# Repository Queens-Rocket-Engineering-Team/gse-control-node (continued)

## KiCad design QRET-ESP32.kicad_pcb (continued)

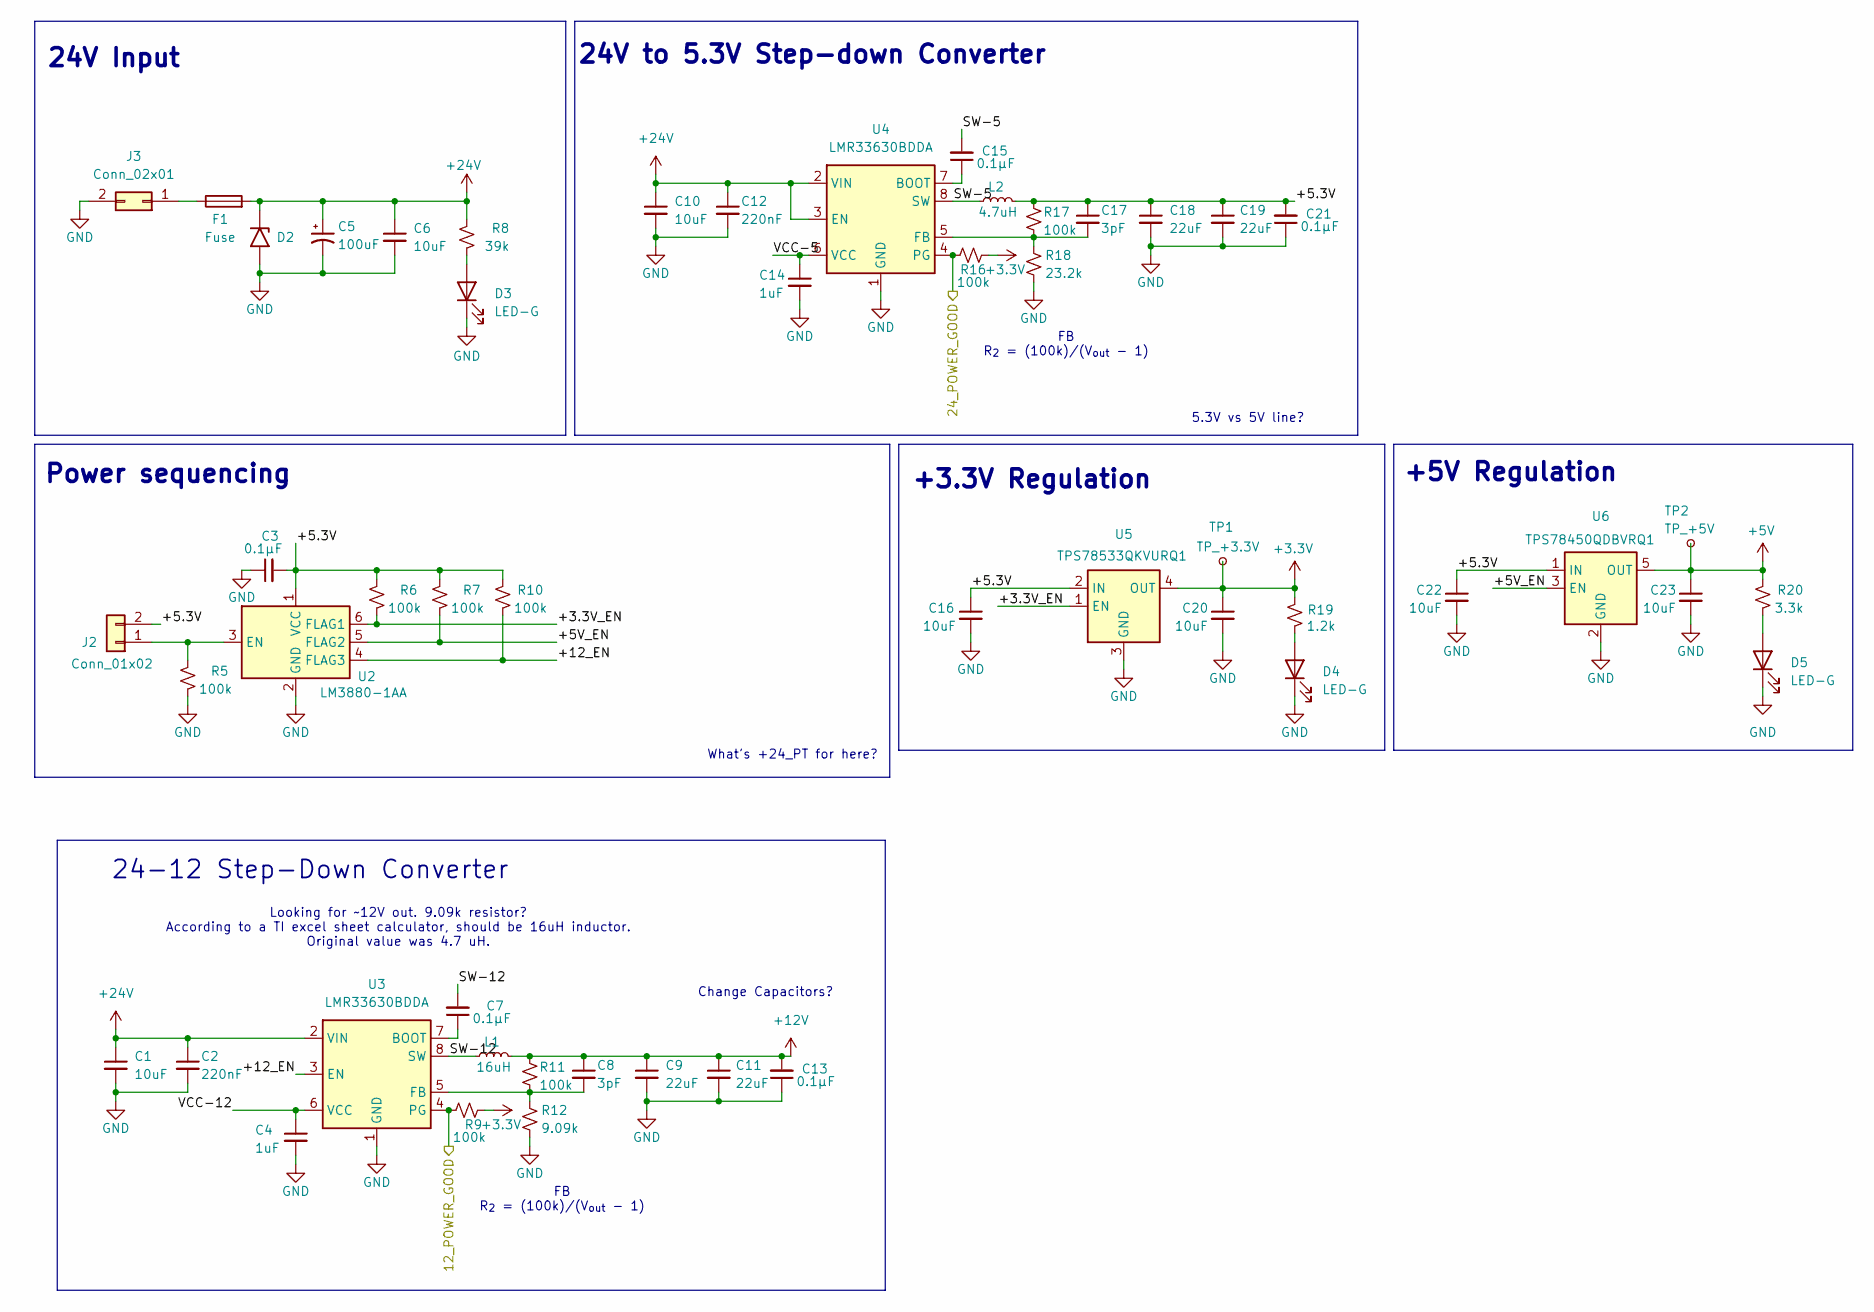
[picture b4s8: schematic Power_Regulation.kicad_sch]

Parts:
C1, C10: 10uF; C_1206_3216Metric; Voltage 50V; LCSC C13585
C2, C12: 220nF; C_0805_2012Metric; Voltage 50V; LCSC C5378
C3, C7, C13, C15, C21: 0.1μF; C_0402_1005Metric; MPN CL05B104KO5NNNC; LCSC C307331
C4, C14: 1uF; C_0603_1608Metric; LCSC C29936
C5: 100uF; CP_Elec_10x10; LCSC C161937
C6: 10uF; C_1812_4532Metric; Voltage 50V
C8, C17: 3pF; C_0603_1608Metric; LCSC C695157
C9, C11, C18, C19: 22uF; C_0805_2012Metric; LCSC C602037
C16, C20, C22, C23: 10uF; C_0805_2012Metric; LCSC C15850
D2: SMCJ26A-13-F; D_SMC; LCSC C135156
D3, D4, D5: LED-G; LED_0805_2012Metric; LCSC C2297
F1: Fuse; Fuseholder_Blade_Mini_Keystone_3568
J2: Conn_01x02; Molex_Micro-Fit_3.0_43650-0215_1x02_P3.00mm_Vertical
J3: Conn_02x01; Molex_Mini-Fit_Jr_5566-02A_2x01_P4.20mm_Vertical
L1: 16uH; L_Bourns_SRP7028A_7.3x6.6mm; LCSC C840529
L2: 4.7uH; L_Bourns_SRP7028A_7.3x6.6mm; LCSC C840529
R5, R6, R7, R10: 100k; R_0603_1608Metric
R8: 39k; R_0402_1005Metric
R9, R11, R16, R17: 100k; R_0603_1608Metric; MPN 0402WGJ0103TCE; LCSC C25531
R12: 9.09k; R_0603_1608Metric; MPN 0402WGF3301TCE; LCSC C25890
R18: 23.2k; R_0603_1608Metric; MPN 0402WGF3301TCE; LCSC C25890
R19: 1.2k; R_0402_1005Metric
R20: 3.3k; R_0402_1005Metric
TP1: TP_+3.3V; TestPoint_Pad_D1.0mm
TP2: TP_+5V; TestPoint_Pad_D1.0mm
U2: LM3880-1AA; SOT-23-6; LCSC C486059
U3, U4: LMR33630BDDA; Texas_HSOP-8-1EP_3.9x4.9mm_P1.27mm_ThermalVias; LCSC C544370
U5: TPS78533QKVURQ1; TO-252-4; LCSC C3748131
U6: TPS78450QDBVRQ1; SOT-23-5; LCSC C2877783

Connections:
12V_GOOD: R9.1, U3.4 (PG); also elsewhere on the board
24V_GOOD: R16.1, U4.4 (PG); also elsewhere on the board
+5V: C23.1, R20.2, TP2.1, U6.5 (OUT); also elsewhere on the board
+12V: C8.1, C9.1, C11.1, C13.2, L1.2, R11.1; also elsewhere on the board
+24V: C1.1, C2.1, C5.1, C6.1, C10.1, C12.1, D2.1 (A1), F1.2, R8.2, U3.2 (VIN), U4.2 (VIN), U4.3 (EN); also elsewhere on the board
/Power_Regulation/+3.3V_EN: R6.1, U2.6 (FLAG1), U5.1 (EN)
/Power_Regulation/+5.3V: C3.2, C16.1, C17.1, C18.1, C19.1, C21.2, C22.1, J2.2, L2.2, R6.2, R7.2, R10.2, R17.1, U2.1 (VCC), U5.2 (IN), U6.1 (IN)
/Power_Regulation/+5V_EN: R7.1, U2.5 (FLAG2), U6.3 (EN)
/Power_Regulation/+12_EN: R10.1, U2.4 (FLAG3), U3.3 (EN)
/Power_Regulation/SW-5: C15.2, L2.1, U4.8 (SW)
/Power_Regulation/SW-12: C7.2, L1.1, U3.8 (SW)
/Power_Regulation/VCC-5: C14.1, U4.6 (VCC)
/Power_Regulation/VCC-12: C4.1, U3.6 (VCC)
unnamed: D3.2 (A), R8.1
unnamed: D4.2 (A), R19.1
unnamed: D5.2 (A), R20.1
unnamed: J2.1, R5.2, U2.3 (EN)
unnamed: F1.1, J3.1
unnamed: C7.1, U3.7 (BOOT)
unnamed: C8.2, R11.2, R12.1, U3.5 (FB)
unnamed: C15.1, U4.7 (BOOT)
unnamed: C17.2, R17.2, R18.1, U4.5 (FB)

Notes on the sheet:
24V Input
5.3V vs 5V line?
24V to 5.3V Step-down Converter
What's +24_PT for here?
FB R_{2} = (100k)/(V_{out} - 1)
+3.3V Regulation
Change Capacitors?
Power sequencing
+5V Regulation
Looking for ~12V out. 9.09k resistor? According to a TI excel sheet calculator, should be 16uH inductor. Original value was 4.7 uH.
24-12 Step-Down Converter

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
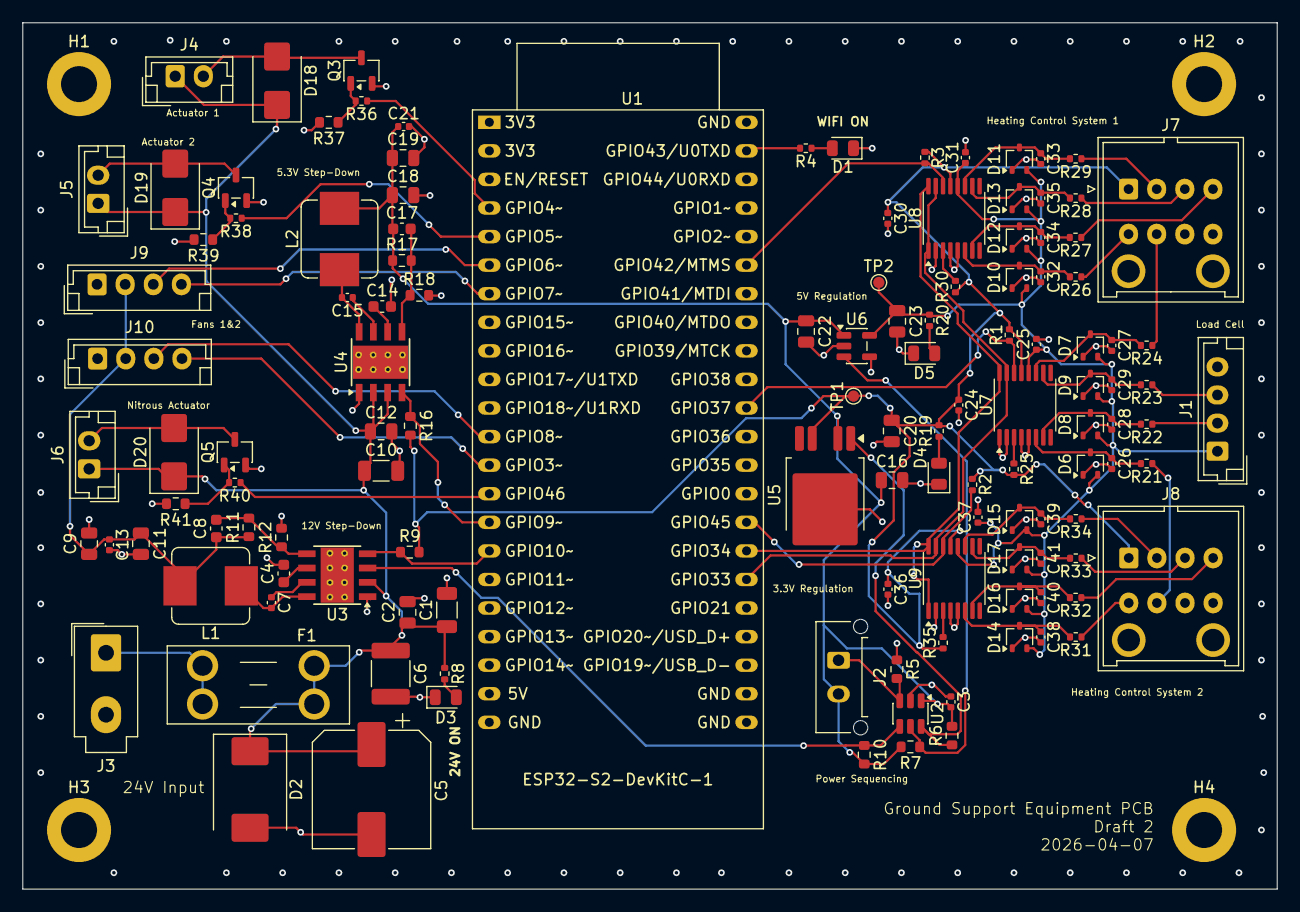
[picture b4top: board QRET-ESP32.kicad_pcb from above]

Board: 4 copper layers, 111.5 x 77.0 mm, 130 parts (0 on the bottom side), 71 nets.

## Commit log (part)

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2026-04-07 Placed the general sets of components.
2026-04-07 General board shape, mounting holes, grounding plates.
2026-04-07 Second draft of placement and wiring.
2026-04-07 Added labels and notes.
2026-05-27 update project to kicad v10
2026-05-28 remove thermistors from board
2026-05-29 rename project to be more descriptive
2026-05-29 fix load cell connector
2026-05-29 switch to on-board esp32s3
2026-05-29 fix fan header footprint
2026-05-30 update buck converter components and add reverse polarity protection
2026-05-30 do some pcb routing
2026-05-30 finish pcb routing
2026-05-31 remove unneccesary component fields
2026-05-31 add all lcsc part numbers
2026-05-31 add readme
2026-05-31 add thermal reliefs on bottom power planes
2026-05-31 give more clearance for load cell connector from edge of board
2026-05-31 fix 5.17V buck switch node net name
2026-05-31 switch to esp32-s3-wroom-1
2026-05-31 update some routing and put ground pour on top layer to avoid warping
2026-05-31 update silkscreen
2026-05-31 update all capacitors to jlcpcb basic components
2026-05-31 add a 12v testpoint
2026-05-31 update resistors to jlcpcb basic components
2026-06-01 fix copper pour priorities
2026-06-01 move up ads112c04 capacitors further from pins for easier handsoldering
2026-06-01 remove some extended components from bom (to be handsoldered)
2026-06-01 update screw terminal footprint
2026-06-01 add tachometer pullup and pwm low side fet for fans
2026-06-01 organize hierarchical sheet page numbers
2026-06-04 update gitignore
2026-06-04 add back bss138 to jlcpcb bom
2026-06-05 switch load cell connector to 5 pin with shield
2026-06-05 fix load cell silkscreen
2026-06-09 add heater connectors
2026-06-11 add heater power regulation for fet switching
2026-06-11 seperate board directories and finish heater driver routing
2026-06-17 add relay to heater board for estop and do some ignitor board routing
2026-06-18 finish ignitor board routing
2026-06-23 finish control board routing
2026-06-24 updates for manufacturing
